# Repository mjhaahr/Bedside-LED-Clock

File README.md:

# RGB LED 7-Segment Bedside Clock with Ambient Light and Proximity Sensor

## Features
- USB C Port for Power, Comms, and Programming
    - Connects to the ESP32-C3's onboard USB-CDC/JTAG device
- ESP32-C3 Module for control
    - Allows pattern changing over WiFi/Bluetooth, as well as the buttons on the device
- Integrated Ambient Light and Proximity Sensor
    - Allows the clock to be used at night and stay idle unless desired
- 86 Addressable RGB LEDs
    - APA102-style (DotStar) 2-Wire Control with Global Dimmer and Clock
    - HD107S-5050
    
## Table Of Contents
- [Features](#features)
- [Bill Of Materials](#bill-of-materials)
- [Part Selection](#part-selection)
- [Case Design](#case-design)
- [Code](#code)
- [Extra Notes](#extra-notes)

## Bill of Materials
<!--  
- NAME - FUNC
    - Component: REF
    - Quantity: 
    - [Datasheet]()
    - [DigiKey]()
-->
- Espressif ESP32-C3-MINI-1 - Microcontroller Module w/ WiFi and Bluetooth
    - Component: U1
    - Quantity: 1
    - [Datasheet](https://www.espressif.com/sites/default/files/documentation/esp32-c3-mini-1_datasheet_en.pdf)
    - [DigiKey](https://www.digikey.com/en/products/detail/espressif-systems/ESP32-C3-MINI-1-N4-A/15817506)
- STMicroelectronics USBLC6-2SC6 - USB Data and Power TVS Diode
    - Component: U2
    - Quantity: 1
    - [Datasheet](https://www.st.com/content/ccc/resource/technical/document/datasheet/06/1d/48/9c/6c/20/4a/b2/CD00050750.pdf/files/CD00050750.pdf/jcr:content/translations/en.CD00050750.pdf)
    - [DigiKey](https://www.digikey.com/en/products/detail/stmicroelectronics/USBLC6-2SC6/1040559)
- Vishay VCNL4040M3OE - Combination Ambient Light and Proximity Sensor
    - Component: U3
    - Quantity: 1
    - [Datasheet](https://www.vishay.com/docs/84274/vcnl4040.pdf)
    - [DigiKey](https://www.digikey.com/en/products/detail/vishay-semiconductor-opto-division/VCNL4040M3OE/5171283)
- TI SN74LVC2T45DCTR - Two Channel Fast Level Shifter (from 3V3 MCU to 5V LEDs)
    - Component: U4
    - Quantity: 1
    - [Datasheet](https://www.ti.com/lit/ds/symlink/sn74lvc2t45.pdf)
    - [DigiKey](https://www.digikey.com/en/products/detail/texas-instruments/SN74LVC2T45DCTR/639457)
- Microchip MCP1825ST-3302E/DB - 3V3 Low Noise LDO (500mA)
    - Component: U5
    - Quantity: 1
    - [Datasheet](https://ww1.microchip.com/downloads/en/DeviceDoc/22056b.pdf)
    - [DigiKey](https://www.digikey.com/en/products/detail/microchip-technology/MCP1825ST-3302E-DB/1635518)
- HD107S - APA102 Style Addressable RGB LED with Global Dimmer and Clock 
    - Component: D1 - D86
    - Quantity: 86
    - [Datasheet](https://cdn.hackaday.io/files/1677667177700544/HD107S%20%20Pixel%20RGB%205050%20LED%20chip%20%20Specificaion%20V1.0.1.pdf)
    - [LED Lighting Hut](https://www.ledlightinghut.com/hd107s-5050-rgb-led.html)
- Würth Elektronik 150060VS55040 - Green Indicator LED (LED_BUILTIN)
    - Component: D87
    - Quantity: 1
    - [Datasheet](https://www.we-online.com/components/products/datasheet/150060VS55040.pdf)
    - [DigiKey](https://www.digikey.com/en/products/detail/w%C3%BCrth-elektronik/150060VS55040/8557182)
- GCT USB4520-03-0-A - Midmount USB 2.0 Type C Port
    - Component: J1
    - Quantity: 1
    - [Datasheet](https://gct.co/files/specs/usb4520-spec.pdf)
    - [DigiKey](https://www.digikey.com/en/products/detail/gct/USB4520-03-0-A/15283199)
- E-Switch TL6330AF200Q - Tactile Normally Open Push Button 
    - Component: SW1 - SW4
    - Quantity: 4
    - [Datasheet](https://configured-product-images.s3.amazonaws.com/Datasheets/TL6330.pdf)
    - [DigiKey](https://www.digikey.com/en/products/detail/e-switch/TL6330AF200Q/8032037)
- 100nF - Yageo 0603 Ceramic Capacitor
    - Component: C1 - C86, C89, C91, C96, C98, C99
    - Quantity: 13
    - [DigiKey](https://www.digikey.com/en/products/detail/yageo/CC0603KRX7R7BB104/302822)
- 1µF - Yageo 0603 Ceramic Capacitor
    - Component: C87, C92, C102
    - Quantity: 3
    - [DigiKey](https://www.digikey.com/en/products/detail/yageo/CC0603KRX5R8BB105/2833610)
- 10µF - Yageo 0603 Ceramic Capacitor
    - Component: C88, C90, C97
    - Quantity: 3
    - [DigiKey](https://www.digikey.com/en/products/detail/yageo/CC0603MRX5R6BB106/5195224)
- 22pF - Yageo 0603 Ceramic Capacitor
    - Component: C93, C94
    - Quantity: 2
    - [DigiKey](https://www.digikey.com/en/products/detail/yageo/CC0603JRNPO8BN220/5883592)
- 2.2µF - Yageo 0603 Ceramic Capacitor
    - Component: C100
    - Quantity: 1
    - [DigiKey](https://www.digikey.com/en/products/detail/yageo/CC0603KRX5R7BB225/5195192)
- 4.7µF - Yageo 0603 Ceramic Capacitor
    - Component: C101
    - Quantity: 1
    - [DigiKey](https://www.digikey.com/en/products/detail/yageo/CC0603KRX5R7BB475/5195193)
- 5.1kΩ - Yageo 0603 SMD Resistor
    - Component: R1, R2
    - Quantity: 2
    - [DigiKey](https://www.digikey.com/en/products/detail/yageo/RC0603FR-075K1L/727268)
- 10kΩ - Yageo 0603 SMD Resistor
    - Component: R3, R4, R8, R9
    - Quantity: 4
    - [DigiKey](https://www.digikey.com/en/products/detail/yageo/RC0603FR-1010KL/12756395)
- 1.43kΩ - Yageo 0603 SMD Resistor
    - Component: R5
    - Quantity: 1
    - [DigiKey](https://www.digikey.com/en/products/detail/yageo/RC0603FR-071K43L/726862)
- 0Ω - Yageo 0603 SMD Resistor
    - Component: R6, R7
    - Quantity: 2
    - [DigiKey](https://www.digikey.com/en/products/detail/yageo/RC0603JR-070RL/726675)
- 3.3kΩ - Yageo 0603 SMD Resistor
    - Component: R10, R11
    - Quantity: 2
    - [DigiKey](https://www.digikey.com/en/products/detail/yageo/RC0603FR-073K3L/727126)
- 8.2kΩ - Yageo 0603 SMD Resistor
    - Component: R12
    - Quantity: 1
    - [DigiKey](https://www.digikey.com/en/products/detail/yageo/RC0603FR-078K2L/727390)
- 33Ω - Yageo 0603 SMD Resistor
    - Component: R13 - R16
    - Quantity: 4
    - [DigiKey](https://www.digikey.com/en/products/detail/yageo/RC0603FR-0733RL/727158)

## Case Design
<!--  TODO: Case design needs to be updated  -->
<!--    -->
- 3D Printed Chassis

## Code
<!-- Nothing Written Yet -->
- To view all the code, see it [here](code)

## Extra Notes

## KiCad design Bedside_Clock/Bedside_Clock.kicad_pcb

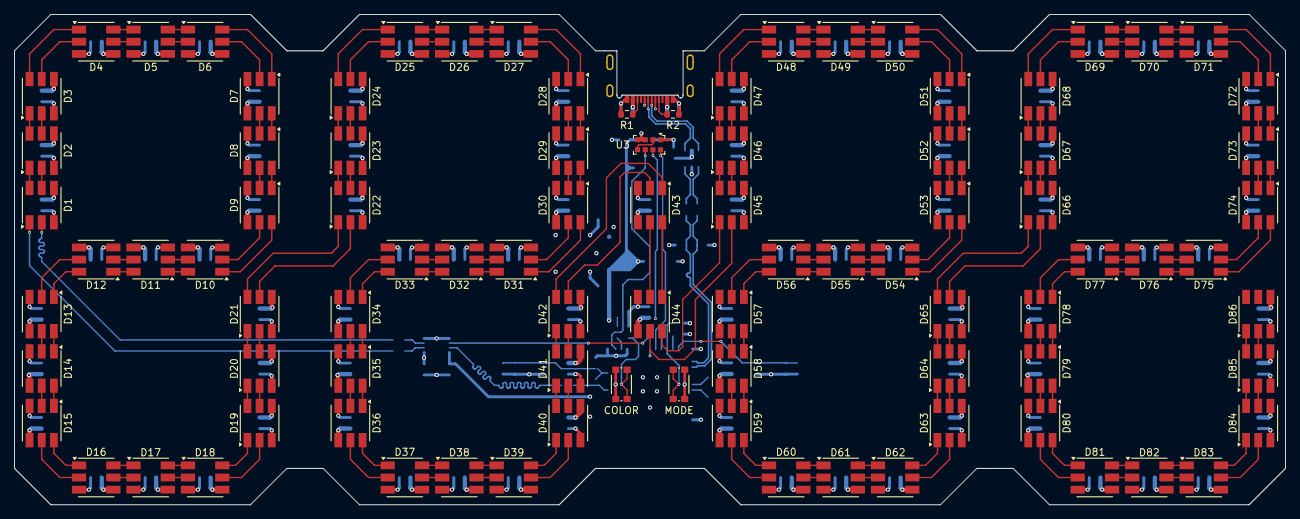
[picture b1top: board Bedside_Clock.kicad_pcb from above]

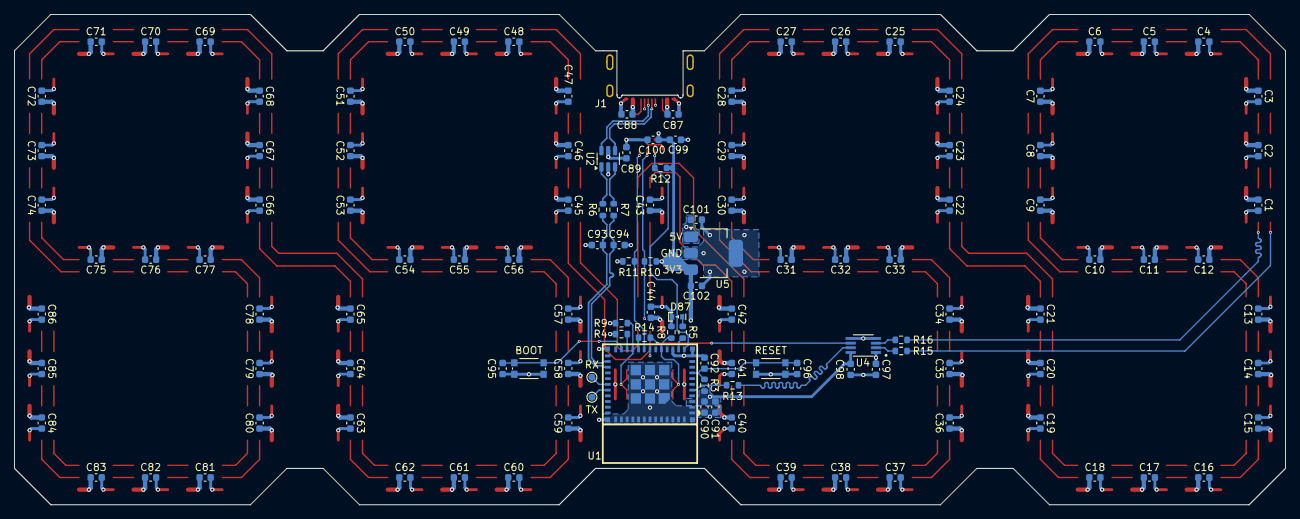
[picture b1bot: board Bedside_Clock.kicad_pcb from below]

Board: 4 copper layers, 177.8 x 68.6 mm, 217 parts (125 on the bottom side), 202 nets.

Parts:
C1, C2, C3, C4, C5, C6, C7, C8, C9, C10, C11, C12, C13, C14, C15, C16, C17, C18, C19, C20, C21, C22, C23, C24, C25, C26, C27, C28, C29, C30, C31, C32, C33, C34, C35, C36, C37, C38, C39, C40, C41, C42, C43, C44, C45, C46, C47, C48, C49, C50, C51, C52, C53, C54, C55, C56, C57, C58, C59, C60, C61, C62, C63, C64, C65, C66, C67, C68, C69, C70, C71, C72, C73, C74, C75, C76, C77, C78, C79, C80, C81, C82, C83, C84, C85, C86, C89, C91, C95, C96, C98, C99: 100nF; C_0603_1608Metric
C87, C92, C102: 1uF; C_0603_1608Metric
C88, C90, C97: 10uF; C_0603_1608Metric
C93, C94: 22pF; C_0603_1608Metric
C100: 2.2uF; C_0603_1608Metric
C101: 4.7uF; C_0603_1608Metric
D1, D2, D3, D4, D5, D6, D7, D8, D9, D10, D11, D12, D13, D14, D15, D16, D17, D18, D19, D20, D21, D22, D23, D24, D25, D26, D27, D28, D29, D30, D31, D32, D33, D34, D35, D36, D37, D38, D39, D40, D41, D42, D43, D44, D45, D46, D47, D48, D49, D50, D51, D52, D53, D54, D55, D56, D57, D58, D59, D60, D61, D62, D63, D64, D65, D66, D67, D68, D69, D70, D71, D72, D73, D74, D75, D76, D77, D78, D79, D80, D81, D82, D83, D84, D85, D86: HD107S; LED_RGB_5050-6
D87: WL-SMCD_0603
J1: USBC_USB2.0; GCT_USB4520-03-0-A_REVA
R1, R2: 5k1; R_0603_1608Metric
R3, R4, R8, R9: 10k; R_0603_1608Metric
R5: 1k43; R_0603_1608Metric
R6, R7: 0; R_0603_1608Metric
R10, R11: 3k3; R_0603_1608Metric
R12: 8k2; R_0603_1608Metric
R13, R14, R15, R16: 33; R_0603_1608Metric
SW1: COLOR; SW_TL6330AF200Q
SW2: MODE; SW_TL6330AF200Q
SW3: BOOT; SW_TL6330AF200Q
SW4: RESET; SW_TL6330AF200Q
TP1: TX; TestPoint_Pad_D1.0mm
TP2: RX; TestPoint_Pad_D1.0mm
U1: ESP32-C3-MINI-1; WIFIM-SMD_ESP32-C3-MINI-1
U2: USBLC6-2SC6; SOT-23-6
U3: VCNL4040M3OE; VISHAY_VCNL4040_4X2X1.1
U4: SN74LVC2T45DCTR; SOP65P400X130-8N
U5: MCP1825S; SOT-223-3_TabPin2

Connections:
+3V3: C90.1, C91.1, C98.1, C99.1, C100.1, C102.1, R3.1, R4.2, R10.2, R11.2, R12.2, SW1.1, SW1.2, SW2.1, SW2.2, U1.3 (3V3), U3.3, U3.4, U4.8 (VCCB), U5.3 (VO)
+5V: C1.1, C2.1, C3.1, C4.1, C5.1, C6.1, C7.1, C8.1, C9.1, C10.1, C11.1, C12.1, C13.1, C14.1, C15.1, C16.1, C17.1, C18.1, C19.1, C20.1, C21.1, C22.1, C23.1, C24.1, C25.1, C26.1, C27.1, C28.1, C29.1, C30.1, C31.1, C32.1, C33.1, C34.1, C35.1, C36.1, C37.1, C38.1, C39.1, C40.1, C41.1, C42.1, C43.1, C44.1, C45.1, C46.1, C47.1, C48.1, C49.1, C50.1, C51.1, C52.1, C53.1, C54.1, C55.1, C56.1, C57.1, C58.1, C59.1, C60.1, C61.1, C62.1, C63.1, C64.1, C65.1, C66.1, C67.1, C68.1, C69.1, C70.1, C71.1, C72.1, C73.1, C74.1, C75.1, C76.1, C77.1, C78.1, C79.1, C80.1, C81.1, C82.1, C83.1, C84.1, C85.1, C86.1, C87.1, C88.1, C89.1, C97.1, C101.1, D1.4 (VCC), D2.4 (VCC), D3.4 (VCC), D4.4 (VCC), D5.4 (VCC), D6.4 (VCC), D7.4 (VCC), D8.4 (VCC), D9.4 (VCC), D10.4 (VCC), D11.4 (VCC), D12.4 (VCC), D13.4 (VCC), D14.4 (VCC), D15.4 (VCC), D16.4 (VCC), D17.4 (VCC), D18.4 (VCC), D19.4 (VCC), D20.4 (VCC), D21.4 (VCC), D22.4 (VCC), D23.4 (VCC), D24.4 (VCC), D25.4 (VCC), D26.4 (VCC), D27.4 (VCC), D28.4 (VCC), D29.4 (VCC), D30.4 (VCC), D31.4 (VCC), D32.4 (VCC), D33.4 (VCC), D34.4 (VCC), D35.4 (VCC), D36.4 (VCC), D37.4 (VCC), D38.4 (VCC), D39.4 (VCC), D40.4 (VCC), D41.4 (VCC), D42.4 (VCC), D43.4 (VCC), D44.4 (VCC), D45.4 (VCC), D46.4 (VCC), D47.4 (VCC), D48.4 (VCC), D49.4 (VCC), D50.4 (VCC), D51.4 (VCC), D52.4 (VCC), D53.4 (VCC), D54.4 (VCC), D55.4 (VCC), D56.4 (VCC), D57.4 (VCC), D58.4 (VCC), D59.4 (VCC), D60.4 (VCC), D61.4 (VCC), D62.4 (VCC), D63.4 (VCC), D64.4 (VCC), D65.4 (VCC), D66.4 (VCC), D67.4 (VCC), D68.4 (VCC), D69.4 (VCC), D70.4 (VCC), D71.4 (VCC), D72.4 (VCC), D73.4 (VCC), D74.4 (VCC), D75.4 (VCC), D76.4 (VCC), D77.4 (VCC), D78.4 (VCC), D79.4 (VCC), D80.4 (VCC), D81.4 (VCC), D82.4 (VCC), D83.4 (VCC), D84.4 (VCC), D85.4 (VCC), D86.4 (VCC), J1.A4_B9 (VBUS), J1.B4_A9 (VBUS), U2.5 (VBUS), U4.1 (VCCA), U5.1 (VI)
/BOOT: C95.1, SW3.1, SW3.2, U1.23 (GPIO9)
/CC1: J1.A5 (CC1), R2.2
/CC2: J1.B5 (CC2), R1.2
/CHIP_EN: C92.1, C96.1, R3.2, SW4.1, SW4.2, U1.8 (EN/CHIP_PU)
/CO: R14.2, U4.6 (B2)
/CO': R14.1, U1.20 (GPIO6)
/CO'': R16.1, U4.3 (A2)
/COLOR: R8.1, SW1.3, SW1.4, U1.16 (GPIO10)
/DO: R13.2, U4.7 (B1)
/DO': R13.1, U1.5 (GPIO2/ADC1_CH2)
/DO'': R15.1, U4.2 (A1)
/Digit0/CI: D1.2 (CI), R16.2
/Digit0/CO: D21.5 (CO), D22.2 (CI)
/Digit0/DI: D1.1 (DI), R15.2
/Digit0/DO: D21.6 (DO), D22.1 (DI)
/Digit1/CO: D42.5 (CO), D43.2 (CI)
/Digit1/DO: D42.6 (DO), D43.1 (DI)
/Digit2/CI: D44.5 (CO), D45.2 (CI)
/Digit2/CO: D65.5 (CO), D66.2 (CI)
/Digit2/DI: D44.6 (DO), D45.1 (DI)
/Digit2/DO: D65.6 (DO), D66.1 (DI)
/LED_BUILTIN: R5.2, U1.13 (GPIO1/ADC1_CH1/XTAL_32K_N)
/MODE: R9.1, SW2.3, SW2.4, U1.21 (GPIO7)
/PROX_INT: R12.1, U1.12 (GPIO0/ADC1_CH0/XTAL_32K_P), U3.6
/SCL: R11.1, U1.19 (GPIO5/ADC2_CH0), U3.8
/SDA: R10.1, U1.18 (GPIO4/ADC1_CH4), U3.7
/UD''+: J1.A6 (D+), J1.B6 (D+), U2.6 (I/O1)
/UD''-: J1.A7 (D-), J1.B7 (D-), U2.4 (I/O2)
/UD'+: C93.1, R6.1, U1.27 (GPIO19/USB_D+)
/UD'-: C94.1, R7.1, U1.26 (GPIO18/USB_D-)
/UD+: R6.2, U2.1 (I/O1)
/UD-: R7.2, U2.3 (I/O2)
GND: C1.2, C2.2, C3.2, C4.2, C5.2, C6.2, C7.2, C8.2, C9.2, C10.2, C11.2, C12.2, C13.2, C14.2, C15.2, C16.2, C17.2, C18.2, C19.2, C20.2, C21.2, C22.2, C23.2, C24.2, C25.2, C26.2, C27.2, C28.2, C29.2, C30.2, C31.2, C32.2, C33.2, C34.2, C35.2, C36.2, C37.2, C38.2, C39.2, C40.2, C41.2, C42.2, C43.2, C44.2, C45.2, C46.2, C47.2, C48.2, C49.2, C50.2, C51.2, C52.2, C53.2, C54.2, C55.2, C56.2, C57.2, C58.2, C59.2, C60.2, C61.2, C62.2, C63.2, C64.2, C65.2, C66.2, C67.2, C68.2, C69.2, C70.2, C71.2, C72.2, C73.2, C74.2, C75.2, C76.2, C77.2, C78.2, C79.2, C80.2, C81.2, C82.2, C83.2, C84.2, C85.2, C86.2, C87.2, C88.2, C89.2, C90.2, C91.2, C92.2, C93.2, C94.2, C95.2, C96.2, C97.2, C98.2, C99.2, C100.2, C101.2, C102.2, D1.3 (GND), D2.3 (GND), D3.3 (GND), D4.3 (GND), D5.3 (GND), D6.3 (GND), D7.3 (GND), D8.3 (GND), D9.3 (GND), D10.3 (GND), D11.3 (GND), D12.3 (GND), D13.3 (GND), D14.3 (GND), D15.3 (GND), D16.3 (GND), D17.3 (GND), D18.3 (GND), D19.3 (GND), D20.3 (GND), D21.3 (GND), D22.3 (GND), D23.3 (GND), D24.3 (GND), D25.3 (GND), D26.3 (GND), D27.3 (GND), D28.3 (GND), D29.3 (GND), D30.3 (GND), D31.3 (GND), D32.3 (GND), D33.3 (GND), D34.3 (GND), D35.3 (GND), D36.3 (GND), D37.3 (GND), D38.3 (GND), D39.3 (GND), D40.3 (GND), D41.3 (GND), D42.3 (GND), D43.3 (GND), D44.3 (GND), D45.3 (GND), D46.3 (GND), D47.3 (GND), D48.3 (GND), D49.3 (GND), D50.3 (GND), D51.3 (GND), D52.3 (GND), D53.3 (GND), D54.3 (GND), D55.3 (GND), D56.3 (GND), D57.3 (GND), D58.3 (GND), D59.3 (GND), D60.3 (GND), D61.3 (GND), D62.3 (GND), D63.3 (GND), D64.3 (GND), D65.3 (GND), D66.3 (GND), D67.3 (GND), D68.3 (GND), D69.3 (GND), D70.3 (GND), D71.3 (GND), D72.3 (GND), D73.3 (GND), D74.3 (GND), D75.3 (GND), D76.3 (GND), D77.3 (GND), D78.3 (GND), D79.3 (GND), D80.3 (GND), D81.3 (GND), D82.3 (GND), D83.3 (GND), D84.3 (GND), D85.3 (GND), D86.3 (GND), D87.1, J1.A1_B12 (GND), J1.B1_A12 (GND), J1.S1 (SHIELD), J1.S2 (SHIELD), J1.S3 (SHIELD), J1.S4 (SHIELD), R1.1, R2.1, R8.2, R9.2, SW3.3, SW3.4, SW4.3, SW4.4, U1.1 (GND), U1.2 (GND), U1.11 (GND), U1.14 (GND), U1.36 (GND), U1.37 (GND), U1.38 (GND), U1.39 (GND), U1.40 (GND), U1.41 (GND), U1.42 (GND), U1.43 (GND), U1.44 (GND), U1.45 (GND), U1.46 (GND), U1.47 (GND), U1.48 (GND), U1.49 (GND), U1.50 (GND), U1.51 (GND), U1.52 (GND), U1.53 (GND), U2.2 (GND), U3.1, U4.4 (GND), U4.5 (DIR), U5.2 (GND)
unnamed: D1.5 (CO), D2.2 (CI)
unnamed: D1.6 (DO), D2.1 (DI)
unnamed: D2.5 (CO), D3.2 (CI)
unnamed: D2.6 (DO), D3.1 (DI)
unnamed: D3.5 (CO), D4.2 (CI)
unnamed: D3.6 (DO), D4.1 (DI)
unnamed: D4.5 (CO), D5.2 (CI)
unnamed: D4.6 (DO), D5.1 (DI)
unnamed: D5.5 (CO), D6.2 (CI)
unnamed: D5.6 (DO), D6.1 (DI)
unnamed: D6.5 (CO), D7.2 (CI)
unnamed: D6.6 (DO), D7.1 (DI)
unnamed: D7.5 (CO), D8.2 (CI)
unnamed: D7.6 (DO), D8.1 (DI)
unnamed: D8.5 (CO), D9.2 (CI)
unnamed: D8.6 (DO), D9.1 (DI)
unnamed: D9.5 (CO), D10.2 (CI)
unnamed: D10.5 (CO), D11.2 (CI)
unnamed: D9.6 (DO), D10.1 (DI)
unnamed: D10.6 (DO), D11.1 (DI)
unnamed: D11.5 (CO), D12.2 (CI)
unnamed: D11.6 (DO), D12.1 (DI)
unnamed: D12.5 (CO), D13.2 (CI)
unnamed: D12.6 (DO), D13.1 (DI)
unnamed: D13.5 (CO), D14.2 (CI)
unnamed: D13.6 (DO), D14.1 (DI)
unnamed: D14.5 (CO), D15.2 (CI)
unnamed: D14.6 (DO), D15.1 (DI)
unnamed: D15.5 (CO), D16.2 (CI)
unnamed: D15.6 (DO), D16.1 (DI)
unnamed: D16.5 (CO), D17.2 (CI)
unnamed: D16.6 (DO), D17.1 (DI)
unnamed: D17.5 (CO), D18.2 (CI)
unnamed: D17.6 (DO), D18.1 (DI)
unnamed: D18.5 (CO), D19.2 (CI)
unnamed: D18.6 (DO), D19.1 (DI)
unnamed: D19.5 (CO), D20.2 (CI)
unnamed: D19.6 (DO), D20.1 (DI)
unnamed: D20.5 (CO), D21.2 (CI)
unnamed: D20.6 (DO), D21.1 (DI)
unnamed: D22.5 (CO), D23.2 (CI)
unnamed: D22.6 (DO), D23.1 (DI)
unnamed: D23.5 (CO), D24.2 (CI)
unnamed: D23.6 (DO), D24.1 (DI)
unnamed: D24.5 (CO), D25.2 (CI)
unnamed: D24.6 (DO), D25.1 (DI)
unnamed: D25.5 (CO), D26.2 (CI)
unnamed: D25.6 (DO), D26.1 (DI)
unnamed: D26.5 (CO), D27.2 (CI)
unnamed: D26.6 (DO), D27.1 (DI)
unnamed: D27.5 (CO), D28.2 (CI)
unnamed: D27.6 (DO), D28.1 (DI)
unnamed: D28.5 (CO), D29.2 (CI)
unnamed: D28.6 (DO), D29.1 (DI)
unnamed: D29.5 (CO), D30.2 (CI)
unnamed: D29.6 (DO), D30.1 (DI)
unnamed: D30.5 (CO), D31.2 (CI)
unnamed: D30.6 (DO), D31.1 (DI)
unnamed: D31.5 (CO), D32.2 (CI)
unnamed: D31.6 (DO), D32.1 (DI)
unnamed: D32.5 (CO), D33.2 (CI)
unnamed: D32.6 (DO), D33.1 (DI)
unnamed: D33.5 (CO), D34.2 (CI)
unnamed: D33.6 (DO), D34.1 (DI)
unnamed: D34.5 (CO), D35.2 (CI)
unnamed: D34.6 (DO), D35.1 (DI)
unnamed: D35.5 (CO), D36.2 (CI)
unnamed: D35.6 (DO), D36.1 (DI)
unnamed: D36.5 (CO), D37.2 (CI)
unnamed: D36.6 (DO), D37.1 (DI)
unnamed: D37.5 (CO), D38.2 (CI)
unnamed: D37.6 (DO), D38.1 (DI)
unnamed: D38.5 (CO), D39.2 (CI)
unnamed: D38.6 (DO), D39.1 (DI)
unnamed: D39.5 (CO), D40.2 (CI)
unnamed: D39.6 (DO), D40.1 (DI)
unnamed: D40.5 (CO), D41.2 (CI)
unnamed: D40.6 (DO), D41.1 (DI)
unnamed: D41.5 (CO), D42.2 (CI)
unnamed: D41.6 (DO), D42.1 (DI)
unnamed: D43.5 (CO), D44.2 (CI)
unnamed: D43.6 (DO), D44.1 (DI)
unnamed: D45.5 (CO), D46.2 (CI)
unnamed: D45.6 (DO), D46.1 (DI)
unnamed: D46.5 (CO), D47.2 (CI)
unnamed: D46.6 (DO), D47.1 (DI)
unnamed: D47.5 (CO), D48.2 (CI)
unnamed: D47.6 (DO), D48.1 (DI)
unnamed: D48.5 (CO), D49.2 (CI)
unnamed: D48.6 (DO), D49.1 (DI)
unnamed: D49.5 (CO), D50.2 (CI)
unnamed: D49.6 (DO), D50.1 (DI)
unnamed: D50.5 (CO), D51.2 (CI)
unnamed: D50.6 (DO), D51.1 (DI)
unnamed: D51.5 (CO), D52.2 (CI)
unnamed: D51.6 (DO), D52.1 (DI)
unnamed: D52.5 (CO), D53.2 (CI)
unnamed: D52.6 (DO), D53.1 (DI)
unnamed: D53.5 (CO), D54.2 (CI)
unnamed: D53.6 (DO), D54.1 (DI)
unnamed: D54.5 (CO), D55.2 (CI)
unnamed: D54.6 (DO), D55.1 (DI)
unnamed: D55.5 (CO), D56.2 (CI)
unnamed: D55.6 (DO), D56.1 (DI)
unnamed: D56.5 (CO), D57.2 (CI)
unnamed: D56.6 (DO), D57.1 (DI)
unnamed: D57.5 (CO), D58.2 (CI)
unnamed: D57.6 (DO), D58.1 (DI)
unnamed: D58.5 (CO), D59.2 (CI)
unnamed: D58.6 (DO), D59.1 (DI)
unnamed: D59.5 (CO), D60.2 (CI)
unnamed: D59.6 (DO), D60.1 (DI)
unnamed: D60.5 (CO), D61.2 (CI)
unnamed: D60.6 (DO), D61.1 (DI)
unnamed: D61.5 (CO), D62.2 (CI)
unnamed: D61.6 (DO), D62.1 (DI)
unnamed: D62.5 (CO), D63.2 (CI)
unnamed: D62.6 (DO), D63.1 (DI)
unnamed: D63.5 (CO), D64.2 (CI)
unnamed: D63.6 (DO), D64.1 (DI)
unnamed: D64.5 (CO), D65.2 (CI)
unnamed: D64.6 (DO), D65.1 (DI)
unnamed: D66.5 (CO), D67.2 (CI)
unnamed: D66.6 (DO), D67.1 (DI)
unnamed: D67.5 (CO), D68.2 (CI)
unnamed: D67.6 (DO), D68.1 (DI)
unnamed: D68.5 (CO), D69.2 (CI)
unnamed: D68.6 (DO), D69.1 (DI)
unnamed: D69.5 (CO), D70.2 (CI)
unnamed: D69.6 (DO), D70.1 (DI)
unnamed: D70.5 (CO), D71.2 (CI)
unnamed: D70.6 (DO), D71.1 (DI)
unnamed: D71.5 (CO), D72.2 (CI)
unnamed: D71.6 (DO), D72.1 (DI)
unnamed: D72.5 (CO), D73.2 (CI)
unnamed: D72.6 (DO), D73.1 (DI)
unnamed: D73.5 (CO), D74.2 (CI)
unnamed: D73.6 (DO), D74.1 (DI)
unnamed: D74.5 (CO), D75.2 (CI)
unnamed: D74.6 (DO), D75.1 (DI)
unnamed: D75.5 (CO), D76.2 (CI)
unnamed: D75.6 (DO), D76.1 (DI)
unnamed: D76.5 (CO), D77.2 (CI)
unnamed: D76.6 (DO), D77.1 (DI)
unnamed: D77.5 (CO), D78.2 (CI)
unnamed: D77.6 (DO), D78.1 (DI)
unnamed: D78.5 (CO), D79.2 (CI)
unnamed: D78.6 (DO), D79.1 (DI)
unnamed: D79.5 (CO), D80.2 (CI)
unnamed: D79.6 (DO), D80.1 (DI)
unnamed: D80.5 (CO), D81.2 (CI)
unnamed: D80.6 (DO), D81.1 (DI)
unnamed: D81.5 (CO), D82.2 (CI)
unnamed: D81.6 (DO), D82.1 (DI)
unnamed: D82.5 (CO), D83.2 (CI)
unnamed: D82.6 (DO), D83.1 (DI)
unnamed: D83.5 (CO), D84.2 (CI)
unnamed: D83.6 (DO), D84.1 (DI)
unnamed: D84.5 (CO), D85.2 (CI)
unnamed: D84.6 (DO), D85.1 (DI)
unnamed: D85.5 (CO), D86.2 (CI)
unnamed: D85.6 (DO), D86.1 (DI)
unnamed: D87.2, R5.1
unnamed: R4.1, U1.22 (GPIO8)
unnamed: TP2.1, U1.30 (GPIO20/U0RXD)
unnamed: TP1.1, U1.31 (GPIO21/U0TXD)
unnamed: U3.2, U3.5

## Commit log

2025-07-26 [HW] Start schematic work, adddd LEDs (yay for heirarchcial sheets) Lots of TODOs
2025-07-26 [HW] Switch to HD107s (maybe switch to 108s)
2025-07-27 [HW] Layout LEDs and first pass add of ESP32 Also add decoupling caps for all LEDs
2025-07-27 [HW] Swap component names from SK9822 to HD107S
2025-07-27 [HW] Routing progress Need to close on some parts
2025-07-28 [HW] Switch to 4 layers
2025-07-28 [HW] Switch to 4 layers and m mid mount USB-C
2025-07-28 [HW] Clean up and layout improvements
2025-07-31 [HW] Add Ambient Light Sensor and Level Shifter
2025-08-01 [HW] Switch Ambient Light sensor to have proximity
2025-08-02 [HW] Find all parts and finish layout
2025-08-03 [Docs] Start working on Readme e
2025-08-03 [Docs] Add Schematics and Renders Add Diodes, Switches, and Conns to BOM Need Resistors and Capacitors now
2025-08-03 Fix image display issue
2025-08-03 [Docs] Finish BOM
2025-08-13 [HW] Add Series Resistors for SPI/LED Data (can be replaced with 0Ω if necessary) SPI Routing clean up to allow series resistors Also cleaned up some usage notes
